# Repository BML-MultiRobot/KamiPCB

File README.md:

# KamiPCB
Custom PCB for the Kamigami Robot

## Features:

- GPIO pinout for a 40 pin RaspberryPi Zero 2W

- Footprint for a [slide switch](https://www.digikey.com/en/products/detail/w%C3%BCrth-elektronik/450405020524/11631973?utm_adgroup=Slide%20Switches&utm_source=google&utm_medium=cpc&utm_campaign=Shopping_Product_Switches_NEW&utm_term=&utm_content=Slide%20Switches&gclid=Cj0KCQiA4OybBhCzARIsAIcfn9kZlnFyzppiJHsiPTWcjy89dQjPVhE4TyYMwZM6H1WzcRK5DOPNZ7AaApNZEALw_wcB).
    - On position: RaspberryPi Powers On
    - Off position: Charging port is active(can connect the charger)

- Two footprints for [JST connectors](https://www.adafruit.com/product/1769?gclid=Cj0KCQiA4OybBhCzARIsAIcfn9mior_Arr4_kmWMmG2DZCzOcw1qgwyVm_pu0oZZ_99u8Pqh-xn1VJUaAlYnEALw_wcB)
    - Bottom one for [LiPo battery](https://www.adafruit.com/product/2011?gclid=Cj0KCQiA4OybBhCzARIsAIcfn9m_BvMJyWr5UIA2iAXFcFt5TBzUcbMPFACdZFcE9SNztZ2xCmZyJWIaAiT5EALw_wcB) connection
    - Top one for [LiPo Batter Charger](https://www.adafruit.com/product/259?gclid=Cj0KCQiA4OybBhCzARIsAIcfn9mFREJotrwPtDCExjES-GZIEWACWUR3ILdbCu2zyJQ8d5L67fAggNIaAuwoEALw_wcB)

- Pinout for the [motor driver](https://www.sparkfun.com/products/14451?gclid=Cj0KCQiA4OybBhCzARIsAIcfn9nFvoWL2TaoKYcKRDQmxKHgGOQo_j1VHxN8d7iZIITaPM2o-T2BjjAaAgz_EALw_wcB)
    - simply just stacked on via header pins
    - motor leads are routed to the side for easy installation

- Pinout for [8 channel ADC](https://www.adafruit.com/product/856)
    - one channel is already connected to the battery leads for battery voltage measurements

- Footprints for voltage divider step down (all 0805 SMD footprints)
    - one 100kOhm resistor
    - one 180kOhm resistor
    - one 0.1uF capacitor

- Pinout for [9 axis IMU](https://www.adafruit.com/product/3463)

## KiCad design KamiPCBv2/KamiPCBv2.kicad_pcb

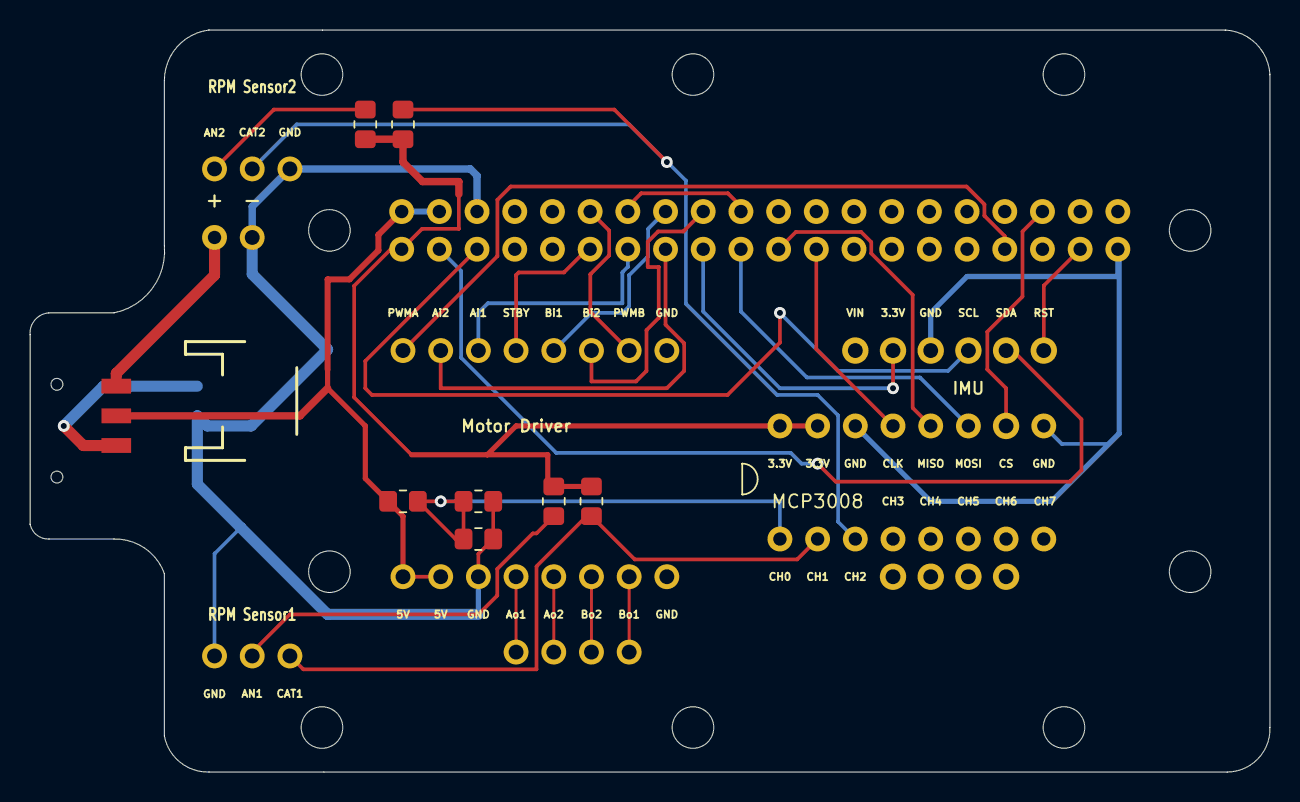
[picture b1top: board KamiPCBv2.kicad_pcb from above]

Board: 2 copper layers, 83.6 x 50.0 mm, 4 parts (0 on the bottom side), 5 nets.

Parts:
FID1: FIDUCIAL""; FIDUCIAL_1MM
JP1: 1X06_ROUND_70
RPI1: KamiPCB; PI_BONNET_NODIM
X1: JSTPH2

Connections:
3.3V: JP1.5, RPI1.1, RPI1.17
5.0V: RPI1.2, RPI1.4
GND: JP1.4, RPI1.6, RPI1.9, RPI1.14, RPI1.20, RPI1.25, RPI1.30, RPI1.34, RPI1.39
SCL: JP1.3, RPI1.5
SDA: JP1.2, RPI1.3

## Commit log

2022-11-22 first five iterations
2022-11-22 Readme updated
2022-11-22 images fixed
2023-08-31 Add files via upload
    Files of Second Generation Kamigami PCB(note: PRE-engineer review).
